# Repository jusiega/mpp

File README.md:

# mpp

morski pomiarowy przyrząd

arduino w folderze mors_ino

autocad w folderdze autocad

kicad w folderze kicad/b

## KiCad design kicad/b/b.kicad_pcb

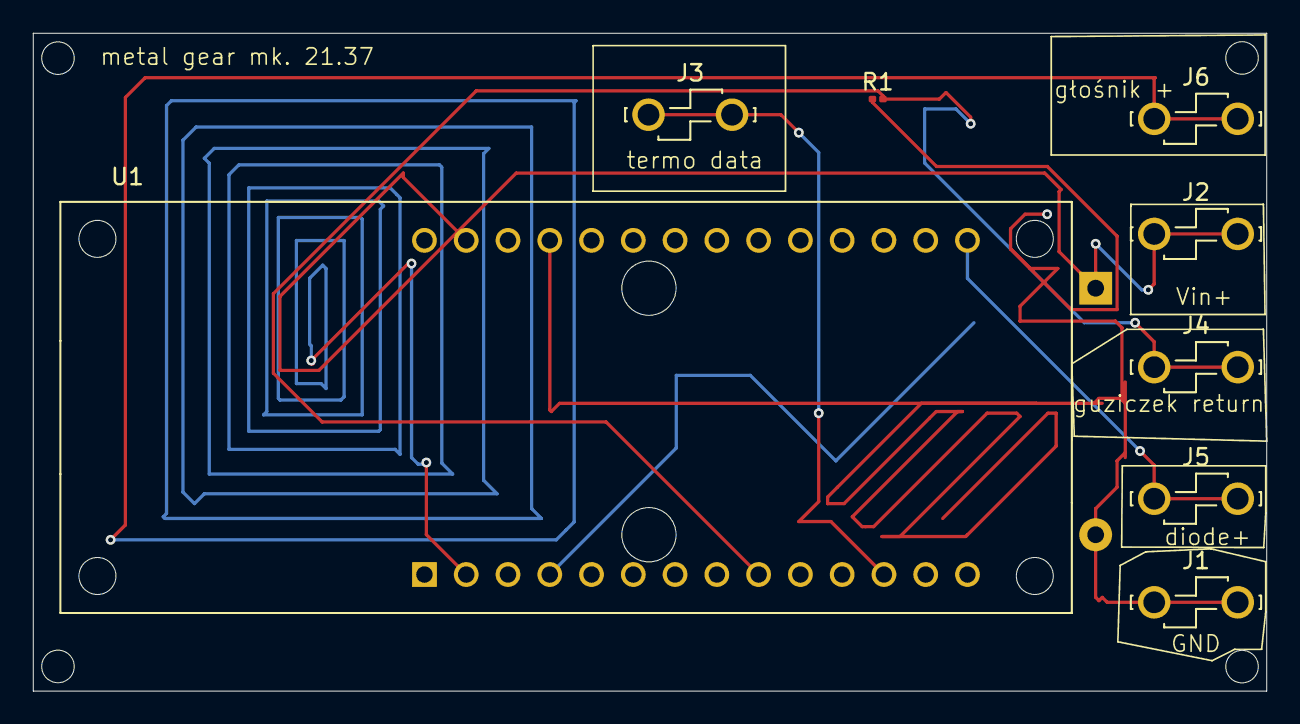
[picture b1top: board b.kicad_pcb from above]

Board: 2 copper layers, 75.0 x 40.0 mm, 9 parts (1 on the bottom side), 6 nets.

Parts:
BT1: Battery_Cell; BatteryHolder_Keystone_2462_2xAA
J1, J2, J3, J4, J5, J6: Conn_01x01_Socket; KEYSTONE_1289-ST
R1: 10000; R_0201_0603Metric
U1: ABX00012; ARDUINO_ABX00012

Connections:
GND: BT1.2 (-), J1.1_1, J1.1_2, R1.1, U1.25 (GND)
unnamed: BT1.1 (+), J2.1_1, J2.1_2, U1.27 (VIN)
unnamed: J3.1_1, J3.1_2, U1.12 (PA11_TCC0-W3/~3)
unnamed: J4.1_1, J4.1_2, R1.2, U1.9 (PA22_TC4-W0/0)
unnamed: J5.1_1, J5.1_2, U1.15 (PA20_TCC0-W6)
unnamed: J6.1_1, J6.1_2, U1.2 (PA02_AIN0/DAC0/A0)

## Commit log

2025-06-22 swwww
2025-06-22 i'm cooomitting
2025-06-24 zajebiście
2025-06-24 kicad done
2025-06-26 final
2025-06-26 final final
